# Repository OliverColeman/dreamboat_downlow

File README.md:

Drive and steering motor and sensor controller code and PCB design for the [Dreamboat](https://github.com/OliverColeman/dreamboat) - a motorised four-poster bed designed to move in surreal and dreamlike ways.

* Connects to the Dreamboat controller (Raspberry Pi) via USB.
* Receives commands that specify the desired drive speed and angles of the wheels.
* Implements servo control for steering of the four wheels.
* Sends telemetry to the Dreamboat controller, including:
  * Wheel steering positions
  * Current draw for each drive and steering motor
  * Battery voltage
* Designed to run on a [Teensy 4.1](https://www.pjrc.com/store/teensy41.html).
* PlatformIO is used for development.

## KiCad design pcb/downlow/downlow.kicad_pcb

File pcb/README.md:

# PCB design for the "downlow" controller

Designed with KiCad 5.99. Main file is `pcb/downlow/downlow.pro`

See `pcb/teensy-4_1-pinout.svg` for the pin assignments for the Teensy.

## Requirements
* https://github.com/Digi-Key/digikey-kicad-library copied to `pcb/digikey-kicad-library-master`
* https://github.com/XenGi/teensy_library copied to `pcb/teensy_library-master`
* https://github.com/XenGi/teensy.pretty copied to `pcb/teensy.pretty`

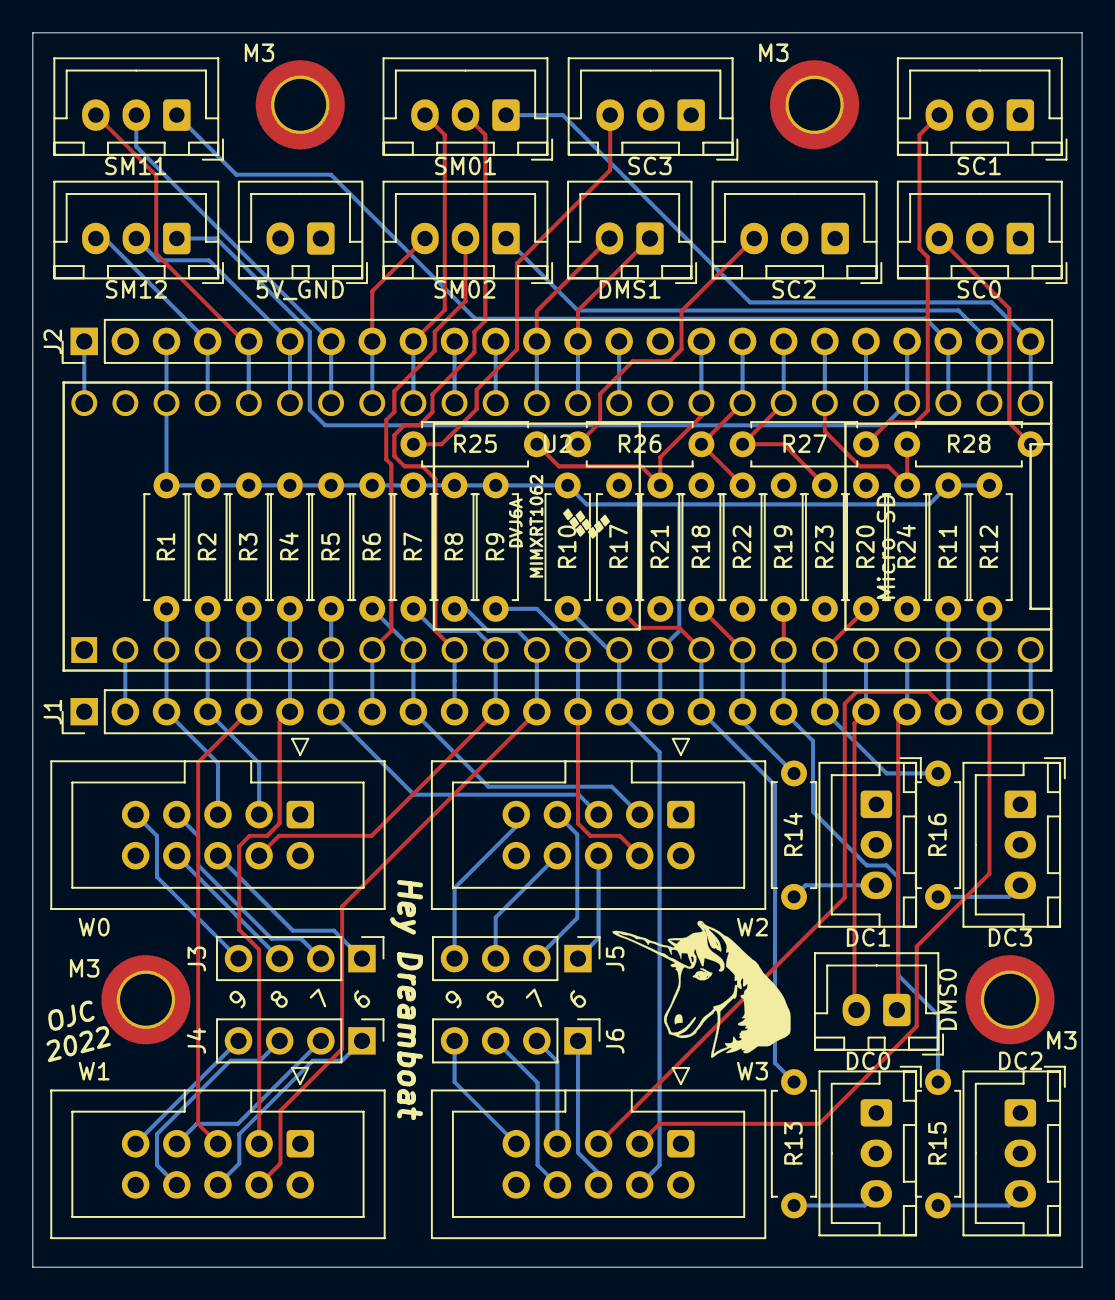
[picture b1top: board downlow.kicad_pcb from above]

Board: 4 copper layers, 64.8 x 76.2 mm, 58 parts (0 on the bottom side), 70 nets.

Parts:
5V_GND: Conn_01x02_Male; JST_XH_B2B-XH-A_1x02_P2.50mm_Vertical
DC0, DC1, DC2, DC3: Conn_01x03_Male; JST_XH_B3B-XH-A_1x03_P2.50mm_Vertical
DMS0, DMS1: Conn_01x02_Male; JST_XH_B2B-XH-A_1x02_P2.50mm_Vertical
J1, J2: Conn_01x24_Male; PinHeader_1x24_P2.54mm_Vertical
J3, J4, J5, J6: Conn_01x04_Male; PinHeader_1x04_P2.54mm_Vertical
M3, M3#2, M3#3, M3#4: MountingHole_3.2mm_M3_ISO14580_Pad_TopBottom
R1, R2, R3, R4, R5, R6, R7, R8, R9, R10, R11, R12, R13, R14, R15, R16, R17, R18, R19, R20, R21, R22, R23, R24, R25, R26, R27, R28: R; R_Axial_DIN0207_L6.3mm_D2.5mm_P7.62mm_Horizontal
SC0, SC1, SC2, SC3: Conn_01x03_Male; JST_XH_B3B-XH-A_1x03_P2.50mm_Vertical
SM01, SM02, SM11, SM12: Conn_01x03_Male; JST_XH_B3B-XH-A_1x03_P2.50mm_Vertical
U2: Teensy4.1; Teensy41_sidepinsonly
W0, W1, W2, W3: Conn_02x05_Odd_Even; IDC-Header_2x05_P2.54mm_Vertical

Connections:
unnamed: 5V_GND.1, DC0.1, DC1.1, DC2.1, DC3.1, J1.1, J2.2, J2.15, R17.1, R18.1, R19.1, R20.1, R21.2, R22.2, R23.2, R24.2, SC0.1, SC1.1, SC2.1, SC3.1, U2.1, U2.34, U2.47, W0.1, W1.1, W2.1, W3.1
unnamed: 5V_GND.2, DC0.2, DC1.2, DC2.2, DC3.2, SC0.2, SC1.2, SC2.2, SC3.2, W0.2, W1.2, W2.2, W3.2
unnamed: DC0.3, R13.2
unnamed: DC1.3, R14.2
unnamed: DC2.3, R15.2
unnamed: DC3.3, R16.2
unnamed: DMS0.1, J1.21, U2.21
unnamed: DMS0.2, J1.20, U2.20
unnamed: DMS1.1, J2.13, U2.36
unnamed: DMS1.2, J2.12, U2.37
unnamed: J1.2, U2.2
unnamed: J1.3, R1.1, U2.3, W0.5
unnamed: J1.4, R2.1, U2.4, W0.3
unnamed: J1.5, R3.1, U2.5, W1.5
unnamed: J1.6, R4.1, U2.6, W1.3
unnamed: J1.7, R5.1, U2.7, W2.5
unnamed: J1.8, SM02.2, U2.8
unnamed: J1.9, R6.1, U2.9, W2.3
unnamed: J1.10, SM01.2, U2.10
unnamed: J1.11, R7.1, U2.11, W0.4
unnamed: J1.12, R8.1, U2.12, W1.4
unnamed: J1.13, R9.1, U2.13, W2.4
unnamed: J1.14, R10.1, U2.14, W3.4
unnamed: J1.15, J2.3, R1.2, R2.2, R3.2, R4.2, R5.2, R6.2, R7.2, R8.2, R9.2, R10.2, R11.2, R12.2, U2.15, U2.46
unnamed: J1.16, R13.1, R17.2, U2.16
unnamed: J1.17, R14.1, R18.2, U2.17
unnamed: J1.18, R15.1, R19.2, U2.18
unnamed: J1.19, R16.1, R20.2, U2.19
unnamed: J1.22, R11.1, U2.22, W3.5
unnamed: J1.23, R12.1, U2.23, W3.3
unnamed: J1.24, U2.24
unnamed: J2.1, U2.48
unnamed: J2.4, SM12.3, U2.45
unnamed: J2.5, SM11.3, U2.44
unnamed: J2.6, SM12.2, U2.43
unnamed: J2.7, SM11.2, U2.42
unnamed: J2.8, SM02.3, U2.41
unnamed: J2.9, SM01.3, U2.40
unnamed: J2.10, U2.39
unnamed: J2.11, U2.38
unnamed: J2.14, U2.35
unnamed: J2.16, R21.1, R25.2, U2.33
unnamed: J2.17, R22.1, R26.2, U2.32
unnamed: J2.18, R23.1, R27.2, U2.31
unnamed: J2.19, R24.1, R28.2, U2.30
unnamed: J2.20, U2.29
unnamed: J2.21, SM12.1, U2.28
unnamed: J2.22, SM11.1, U2.27
unnamed: J2.23, SM02.1, U2.26
unnamed: J2.24, SM01.1, U2.25
unnamed: J3.1, W0.6
unnamed: J3.2, W0.7
unnamed: J3.3, W0.8
unnamed: J3.4, W0.9
unnamed: J4.1, W1.6
unnamed: J4.2, W1.7
unnamed: J4.3, W1.8
unnamed: J4.4, W1.9
unnamed: J5.1, W2.6
unnamed: J5.2, W2.7
unnamed: J5.3, W2.8
unnamed: J5.4, W2.9
unnamed: J6.1, W3.6
unnamed: J6.2, W3.7
unnamed: J6.3, W3.8
unnamed: J6.4, W3.9
unnamed: R25.1, SC3.3
unnamed: R26.1, SC2.3
unnamed: R27.1, SC1.3
unnamed: R28.1, SC0.3

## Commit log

2022-04-17 Initial commit.
2022-04-17 Minor documentation improvements.
2022-05-02 Updates for different motor controller. Bug fixes. Change pin layout.
2022-05-05 Add steering motor driver fault telemetry.
2022-05-07 Use downlow MCU to control drive motors.
2022-05-07 Add current limiting and ramping (for drive) to motor control.
2022-05-18 Various improvements and fixes.
2022-05-21 Added PCB design.
2022-05-21 Added pinout diagram for Teensy. Update main readme.
2023-04-12 Add MOTOR_THROTTLING_FACTOR; settings adjustments.
2023-04-12 Minor updates to PDB.
2023-08-19 Add emergency stop/brake. Reverse rear wheels.
2023-08-20 Add reversed drive motor option.
2025-08-05 Minor fixes and improvements
2025-08-05 Update PCB files for new KiCAD version.
